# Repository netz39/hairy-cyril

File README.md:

hairy-cyril
===========

Inverse Pendulum

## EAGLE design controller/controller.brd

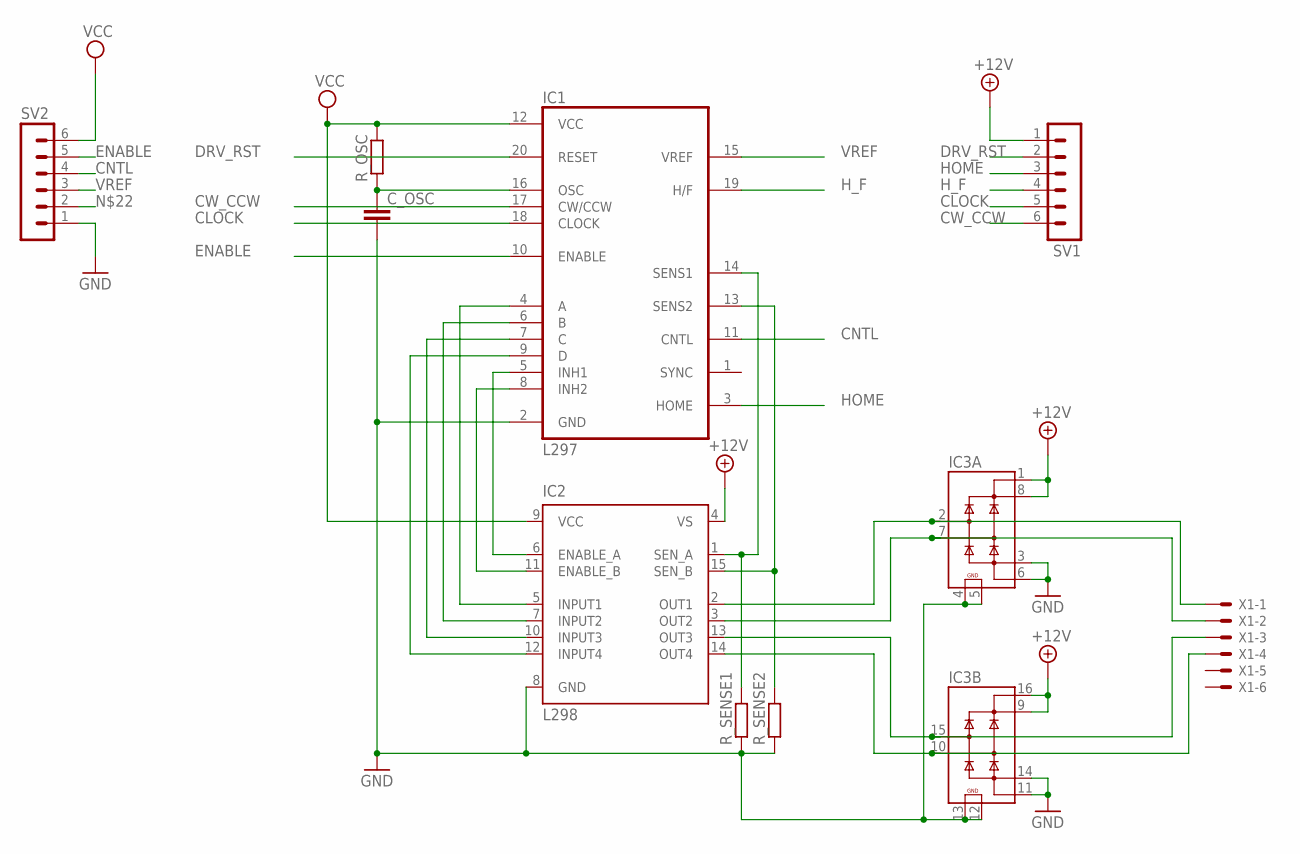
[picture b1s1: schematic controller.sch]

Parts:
C_OSC: C-EU025-030X050; C025-030X050
IC1: L297; DIL20
IC2: L298; MULTIWATT-15
IC3: L6210_2; DIL16
R_OSC: R-EU_0204/7; 0204/7
R_SENSE1, R_SENSE2: R-EU_0204/7; 0204/7
SV1, SV2: MA06-1
X1: 22-23-2061

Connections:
+12V: IC2.4 (VS), IC3.1 (DC1+), IC3.8 (DC2+), IC3.9 (DC2+), IC3.16 (DC1+), SV1.1
CLOCK: IC1.18 (CLOCK), SV1.5
CNTL: IC1.11 (CNTL), SV2.4
CW_CCW: IC1.17 (CW/CCW), SV1.6
DRV_RST: IC1.20 (RESET), SV1.2
ENABLE: IC1.10 (ENABLE), SV2.5
GND: C_OSC.2, IC1.2 (GND), IC2.8 (GND), IC3.3 (DC1-), IC3.4 (GND1), IC3.5 (GND2), IC3.6 (DC2-), IC3.11 (DC2-), IC3.12 (GND2), IC3.13 (GND1), IC3.14 (DC1-), R_SENSE1.1, R_SENSE2.1, SV2.1
HOME: IC1.3 (HOME), SV1.3
H_F: IC1.19 (H/F), SV1.4
unnamed: IC1.4 (A), IC2.5 (INPUT1)
unnamed: IC1.6 (B), IC2.7 (INPUT2)
unnamed: IC1.7 (C), IC2.10 (INPUT3)
unnamed: IC1.9 (D), IC2.12 (INPUT4)
unnamed: IC1.5 (INH1), IC2.6 (ENABLE_A)
unnamed: IC1.8 (INH2), IC2.11 (ENABLE_B)
unnamed: IC1.14 (SENS1), IC2.1 (SEN_A), R_SENSE1.2
unnamed: IC1.13 (SENS2), IC2.15 (SEN_B), R_SENSE2.2
unnamed: IC2.2 (OUT1), IC3.2 (AC1), X1.1
unnamed: IC2.3 (OUT2), IC3.7 (AC2), X1.2
unnamed: IC2.14 (OUT4), IC3.10 (AC2), X1.4
unnamed: IC2.13 (OUT3), IC3.15 (AC1), X1.3
unnamed: C_OSC.1, IC1.16 (OSC), R_OSC.1
VCC: IC1.12 (VCC), IC2.9 (VCC), R_OSC.2, SV2.6
VREF: IC1.15 (VREF), SV2.3

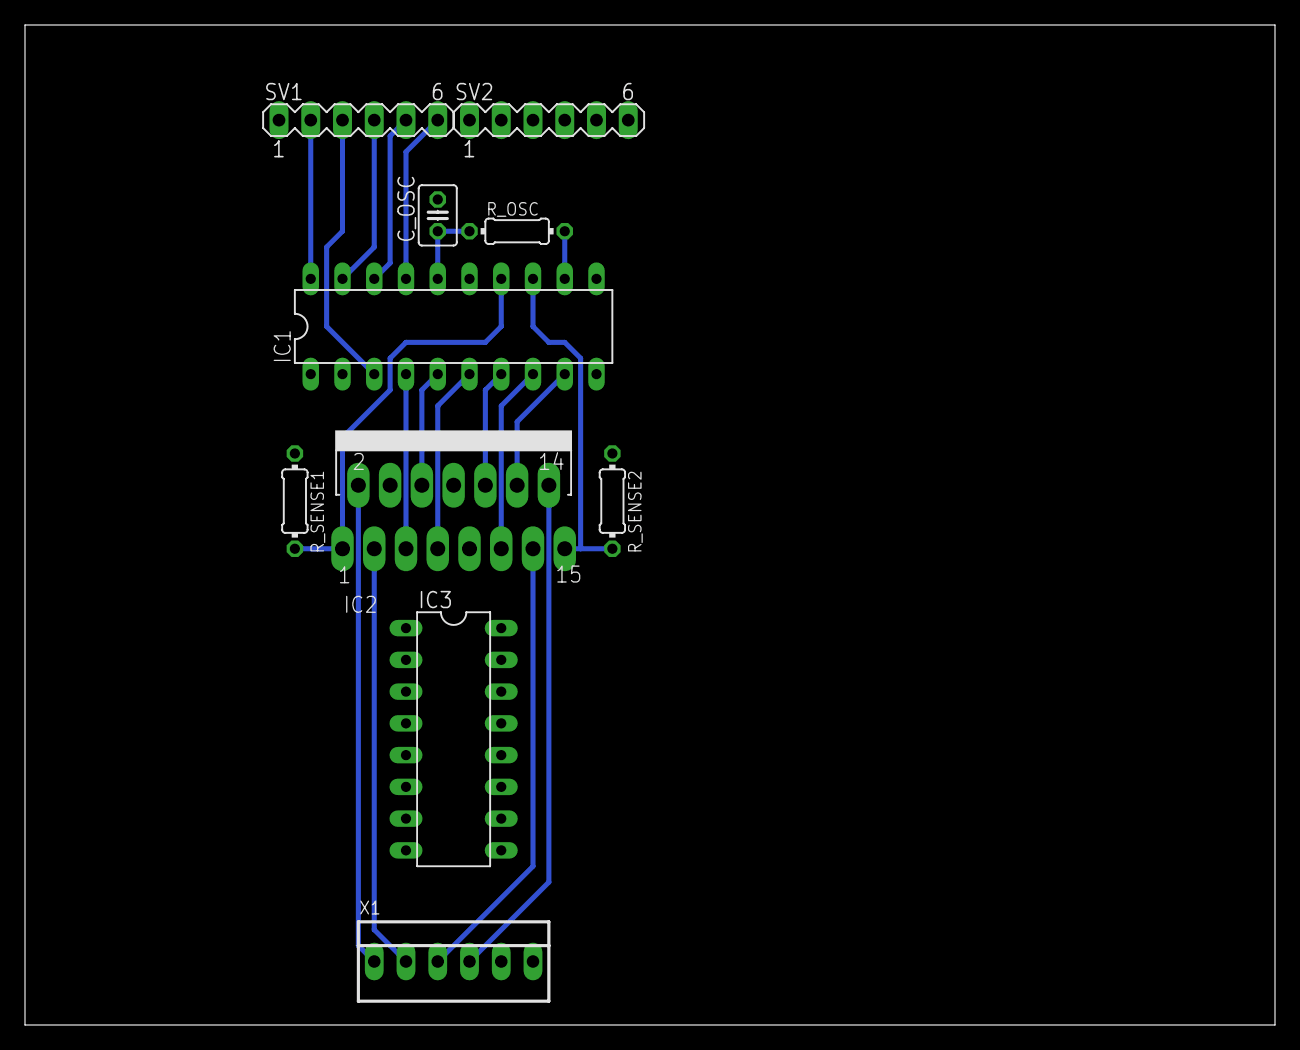
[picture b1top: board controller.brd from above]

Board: 2 copper layers, 100.0 x 80.0 mm, 10 parts (0 on the bottom side), 24 nets.

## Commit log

2013-06-20 initial commit + initial draft of dolly design
2013-06-20 for basti
2013-06-23 cleanup dolly.scad, add dollyaxis.scad,armmount.scad
2013-07-10 Modelle nach models verschoben – hier kommt noch mehr!
2013-07-10 Basis-Schaltung Schrittmotorsteuerung
2013-07-25 new dolly
2013-07-25 dolly finished
2013-07-29 Controllerschaltung weitergebaut
